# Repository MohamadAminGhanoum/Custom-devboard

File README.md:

# Custom-devboard
I will make custom devboard that i can use to create simple projects on my breadboard that do not require soldering. these projects could e.g be make light blink and control simple sensors. 

During this hour, i worked on beginning with the set up of schematic. I followed the guide and learned new things, e.g about the decoupling capacitors and how they function in the circuit. I also learned about how the usb-c is connected in a circuit and what the different pins do.

The finished schematic diagram looks like this:

Then i began building and connecting components  pcb i have built:
The pcb i did was the most complex i have done so far, it was soo tricky because of the small space, especially when connecting to the rp2040 mcu. As seen in this picture, it was difficult to conenct som tracks in such a small spacing, so i had to do a lot of changes to achieve the ending result.

But now, i think the more complex part is here, i have 42 errors i should fix This actually takes a lot of time.

I got to fix all vital errors and ended only with the silkscreen crossing the edgecuts, and this error is normal, because i want the usb-c to go past the board-ending, so it does not matter, however the finished look for pcb looks like this:

The BOM:

LCSC Electronics:

JLCPCB:

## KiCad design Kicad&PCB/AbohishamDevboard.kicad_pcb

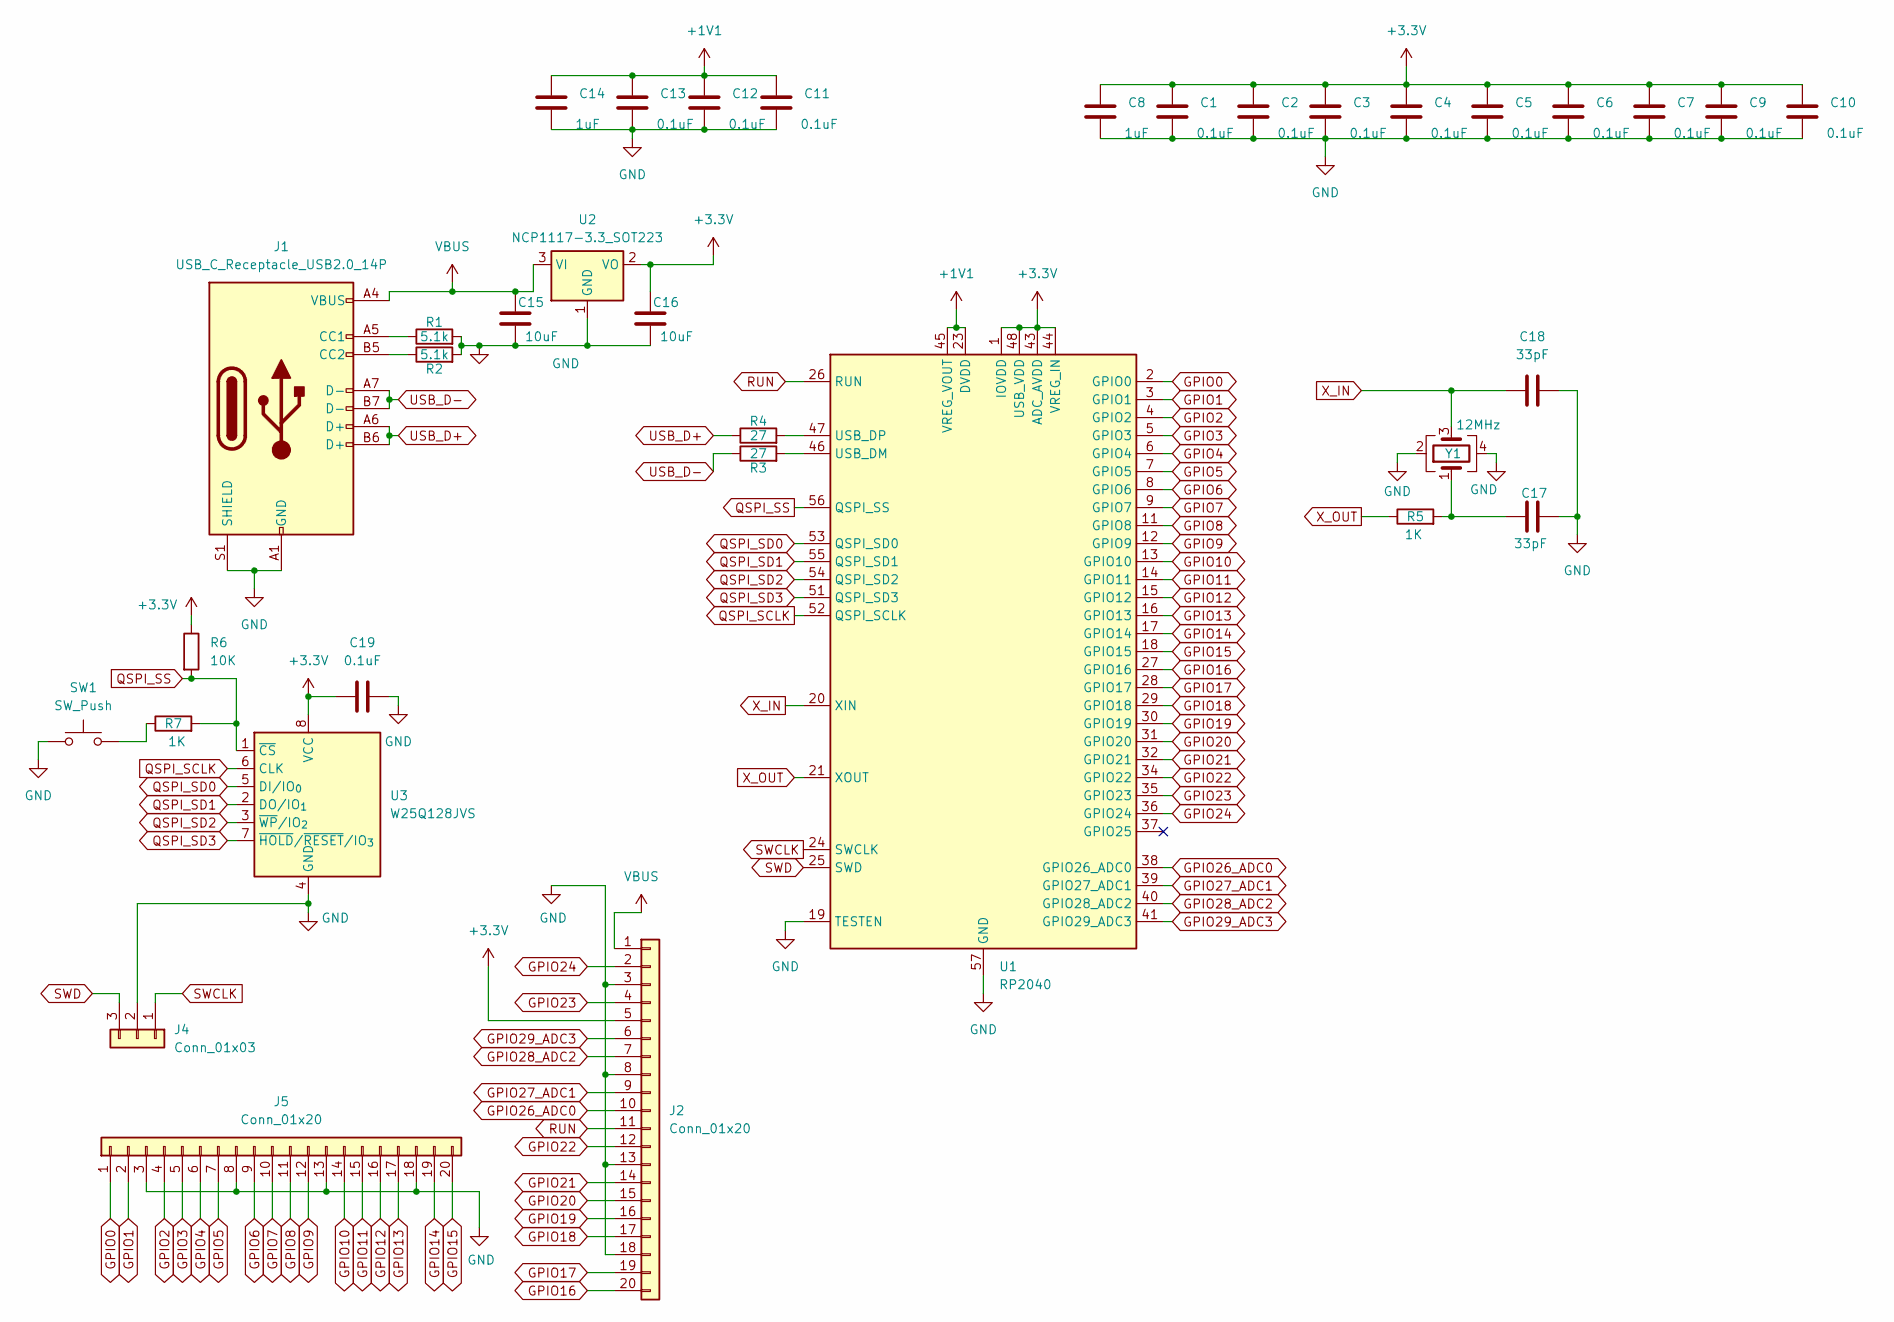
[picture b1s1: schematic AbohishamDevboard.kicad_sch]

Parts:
C1, C2, C3, C4, C5, C6, C7, C9, C10, C11, C12, C13, C19: 0.1uF; C_0402_1005Metric
C8, C14: 1uF; C_0402_1005Metric
C15, C16: 10uF; C_0603_1608Metric
C17, C18: 33pF; C_0402_1005Metric
J1: USB_C_Receptacle_USB2.0_14P; USB_C_Receptacle_HRO_TYPE-C-31-M-12
J2, J5: Conn_01x20; PinHeader_1x20_P2.54mm_Vertical
J4: Conn_01x03; PinHeader_1x03_P2.54mm_Vertical
R1, R2: 5.1k; R_0402_1005Metric
R3, R4: 27; R_0402_1005Metric
R5, R7: 1K; R_0402_1005Metric
R6: 10K; R_0402_1005Metric
SW1: SW_Push; SW_Push_SPST_NO_Alps_SKRK
U1: RP2040; QFN-56-1EP_7x7mm_P0.4mm_EP3.2x3.2mm
U2: NCP1117-3.3_SOT223; SOT-223-3_TabPin2
U3: W25Q128JVS; SOIC-8_5.3x5.3mm_P1.27mm
Y1: 12MHz; Crystal_SMD_3225-4Pin_3.2x2.5mm

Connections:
+1V1: C11.1, C12.1, C13.1, C14.1, U1.23 (DVDD), U1.45 (VREG_VOUT), U1.50 (DVDD)
+3.3V: C1.1, C2.1, C3.1, C4.1, C5.1, C6.1, C7.1, C8.1, C9.1, C10.1, C16.1, C19.1, J2.5, R6.1, U1.1 (IOVDD), U1.10 (IOVDD), U1.22 (IOVDD), U1.33 (IOVDD), U1.42 (IOVDD), U1.43 (ADC_AVDD), U1.44 (VREG_IN), U1.48 (USB_VDD), U1.49 (IOVDD), U2.2 (VO), U3.8 (VCC); also elsewhere on the board
GND: C1.2, C2.2, C3.2, C4.2, C5.2, C6.2, C7.2, C8.2, C9.2, C10.2, C11.2, C12.2, C13.2, C14.2, C15.2, C16.2, C17.2, C18.2, C19.2, J1.A1 (GND), J1.A12 (GND), J1.B1 (GND), J1.B12 (GND), J1.S1 (SHIELD), J2.3, J2.8, J2.13, J2.18, J4.2, J5.3, J5.8, J5.13, J5.18, R1.2, R2.2, SW1.1, U1.19 (TESTEN), U1.57 (GND), U2.1 (GND), U3.4 (GND), Y1.2, Y1.4; also elsewhere on the board
GPIO0: J5.1, U1.2 (GPIO0)
GPIO1: J5.2, U1.3 (GPIO1)
GPIO2: J5.4, U1.4 (GPIO2)
GPIO3: J5.5, U1.5 (GPIO3)
GPIO4: J5.6, U1.6 (GPIO4)
GPIO5: J5.7, U1.7 (GPIO5)
GPIO6: J5.9, U1.8 (GPIO6)
GPIO7: J5.10, U1.9 (GPIO7)
GPIO8: J5.11, U1.11 (GPIO8)
GPIO9: J5.12, U1.12 (GPIO9)
GPIO10: J5.14, U1.13 (GPIO10)
GPIO11: J5.15, U1.14 (GPIO11)
GPIO12: J5.16, U1.15 (GPIO12)
GPIO13: J5.17, U1.16 (GPIO13)
GPIO14: J5.19, U1.17 (GPIO14)
GPIO15: J5.20, U1.18 (GPIO15)
GPIO16: J2.20, U1.27 (GPIO16)
GPIO17: J2.19, U1.28 (GPIO17)
GPIO18: J2.17, U1.29 (GPIO18)
GPIO19: J2.16, U1.30 (GPIO19)
GPIO20: J2.15, U1.31 (GPIO20)
GPIO21: J2.14, U1.32 (GPIO21)
GPIO22: J2.12, U1.34 (GPIO22)
GPIO23: J2.4, U1.35 (GPIO23)
GPIO24: J2.2, U1.36 (GPIO24)
GPIO26_ADC0: J2.10, U1.38 (GPIO26_ADC0)
GPIO27_ADC1: J2.9, U1.39 (GPIO27_ADC1)
GPIO28_ADC2: J2.7, U1.40 (GPIO28_ADC2)
GPIO29_ADC3: J2.6, U1.41 (GPIO29_ADC3)
unnamed: C17.1, R5.2, Y1.1
unnamed: J1.A5 (CC1), R1.1
unnamed: J1.B5 (CC2), R2.1
unnamed: R7.1, SW1.2
unnamed: R3.2, U1.46 (USB_DM)
unnamed: R4.2, U1.47 (USB_DP)
QSPI_SCLK: U1.52 (QSPI_SCLK), U3.6 (CLK)
QSPI_SD0: U1.53 (QSPI_SD0), U3.5 (DI/IO_{0})
QSPI_SD1: U1.55 (QSPI_SD1), U3.2 (DO/IO_{1})
QSPI_SD2: U1.54 (QSPI_SD2), U3.3 (~WP/IO_{2})
QSPI_SD3: U1.51 (QSPI_SD3), U3.7 (~HOLD/~RESET/IO_{3})
QSPI_SS: R6.2, R7.2, U1.56 (QSPI_SS), U3.1 (~CS)
RUN: J2.11, U1.26 (RUN)
SWCLK: J4.1, U1.24 (SWCLK)
SWD: J4.3, U1.25 (SWD)
USB_D+: J1.A6 (D+), J1.B6 (D+), R4.1
USB_D-: J1.A7 (D-), J1.B7 (D-), R3.1
VBUS: C15.1, J1.A4 (VBUS), J1.A9 (VBUS), J1.B4 (VBUS), J1.B9 (VBUS), J2.1, U2.3 (VI)
X_IN: C18.1, U1.20 (XIN), Y1.3
X_OUT: R5.1, U1.21 (XOUT)

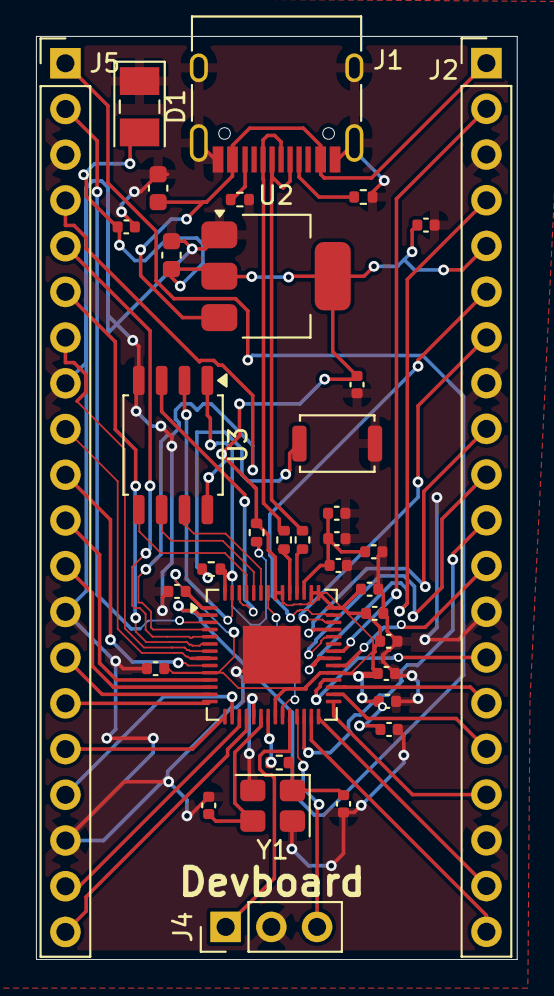
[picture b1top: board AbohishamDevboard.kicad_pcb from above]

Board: 2 copper layers, 26.7 x 51.3 mm, 37 parts (1 on the bottom side), 52 nets.

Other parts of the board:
D1: LED; LED_PLCC-2_3x2mm_KA
Devboard: LOGO

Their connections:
+3.3V: D1.2 (A); also elsewhere on the board
GND: D1.1 (K); also elsewhere on the board

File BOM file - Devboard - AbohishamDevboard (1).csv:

Id,Designator,Footprint,Quantity ,Comment,LCSC part:,Quantity from LCSC electronics,Price from LCSC
1,"C19,C3,C10,C4,C11,C1,C12,C7,C5,C2,C13,C6,C9",C_0402_1005Metric,13,0.1uF,C1525,100,0.12 USD
2,"C17,C18",C_0402_1005Metric,2,33pF,C107005,100,0.11 USD
3,Y1,Crystal_SMD_3225-4Pin_3.2x2.5mm,1,12MHz,C9002,10,0.68 USD
4,"R5,R7",R_0402_1005Metric,2,1K,C106235,100,0.07 USD
5,"J2,J5",PinHeader_1x20_P2.54mm_Vertical,2,Conn_01x20,C50981,5,0.53 USD
6,"C8,C14",C_0402_1005Metric,2,1uF,C14445,100,0.17 USD
7,U1,QFN-56-1EP_7x7mm_P0.4mm_EP3.2x3.2mm,1,RP2040,C2040,1,0.95 USD
8,R6,R_0402_1005Metric,1,10K,C60490,100,0.06 USD
9,"C16,C15",C_0603_1608Metric,2,10uF,C19702,50,0.29 USD
10,"R1,R2",R_0402_1005Metric,2,5.1k,C25905,100,0.06 USD
11,J1,USB_C_Receptacle_HRO_TYPE-C-31-M-12,1,USB_C_Receptacle_USB2.0_14P,C165948,5,0.88 USD
12,U3,SOIC-8_5.3x5.3mm_P1.27mm,1,W25Q128JVS,C97521,1,1.64 USD
13,"R3,R4",R_0402_1005Metric,2,27ohm ,C138021,100,0.08 USD
14,J4,PinHeader_1x03_P2.54mm_Vertical,1,Conn_01x03,C92159,20,0.37 USD
15,U2,SOT-223-3_TabPin2,1,NCP1117-3.3_SOT223,C26537,5,1.18 USD
16,SW1,SW_Push_SPST_NO_Alps_SKRK,1,SW_Push,C202388,5,0.84 USD
17,LED,Red LED indicator,1,SMD_LED,C19171390,100,0.57 USD

,PCB,PCB ,5,from JLCPCB(4USD),NA,,

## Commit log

2026-01-01 Rename Production.zip to Production/Production.zip
2026-01-01 Rename AbohishamDevboard.kicad_pro to Kicad&PCB/AbohishamDevboard.kicad_pro
2026-01-01 Rename Screenshot 2026-01-01 at 15.13.54.png to assets/Screenshot 2026-01-01 at 15.13.54.png
2026-01-06 Rename Devboard - this.zip to production/Devboard - this.zip
